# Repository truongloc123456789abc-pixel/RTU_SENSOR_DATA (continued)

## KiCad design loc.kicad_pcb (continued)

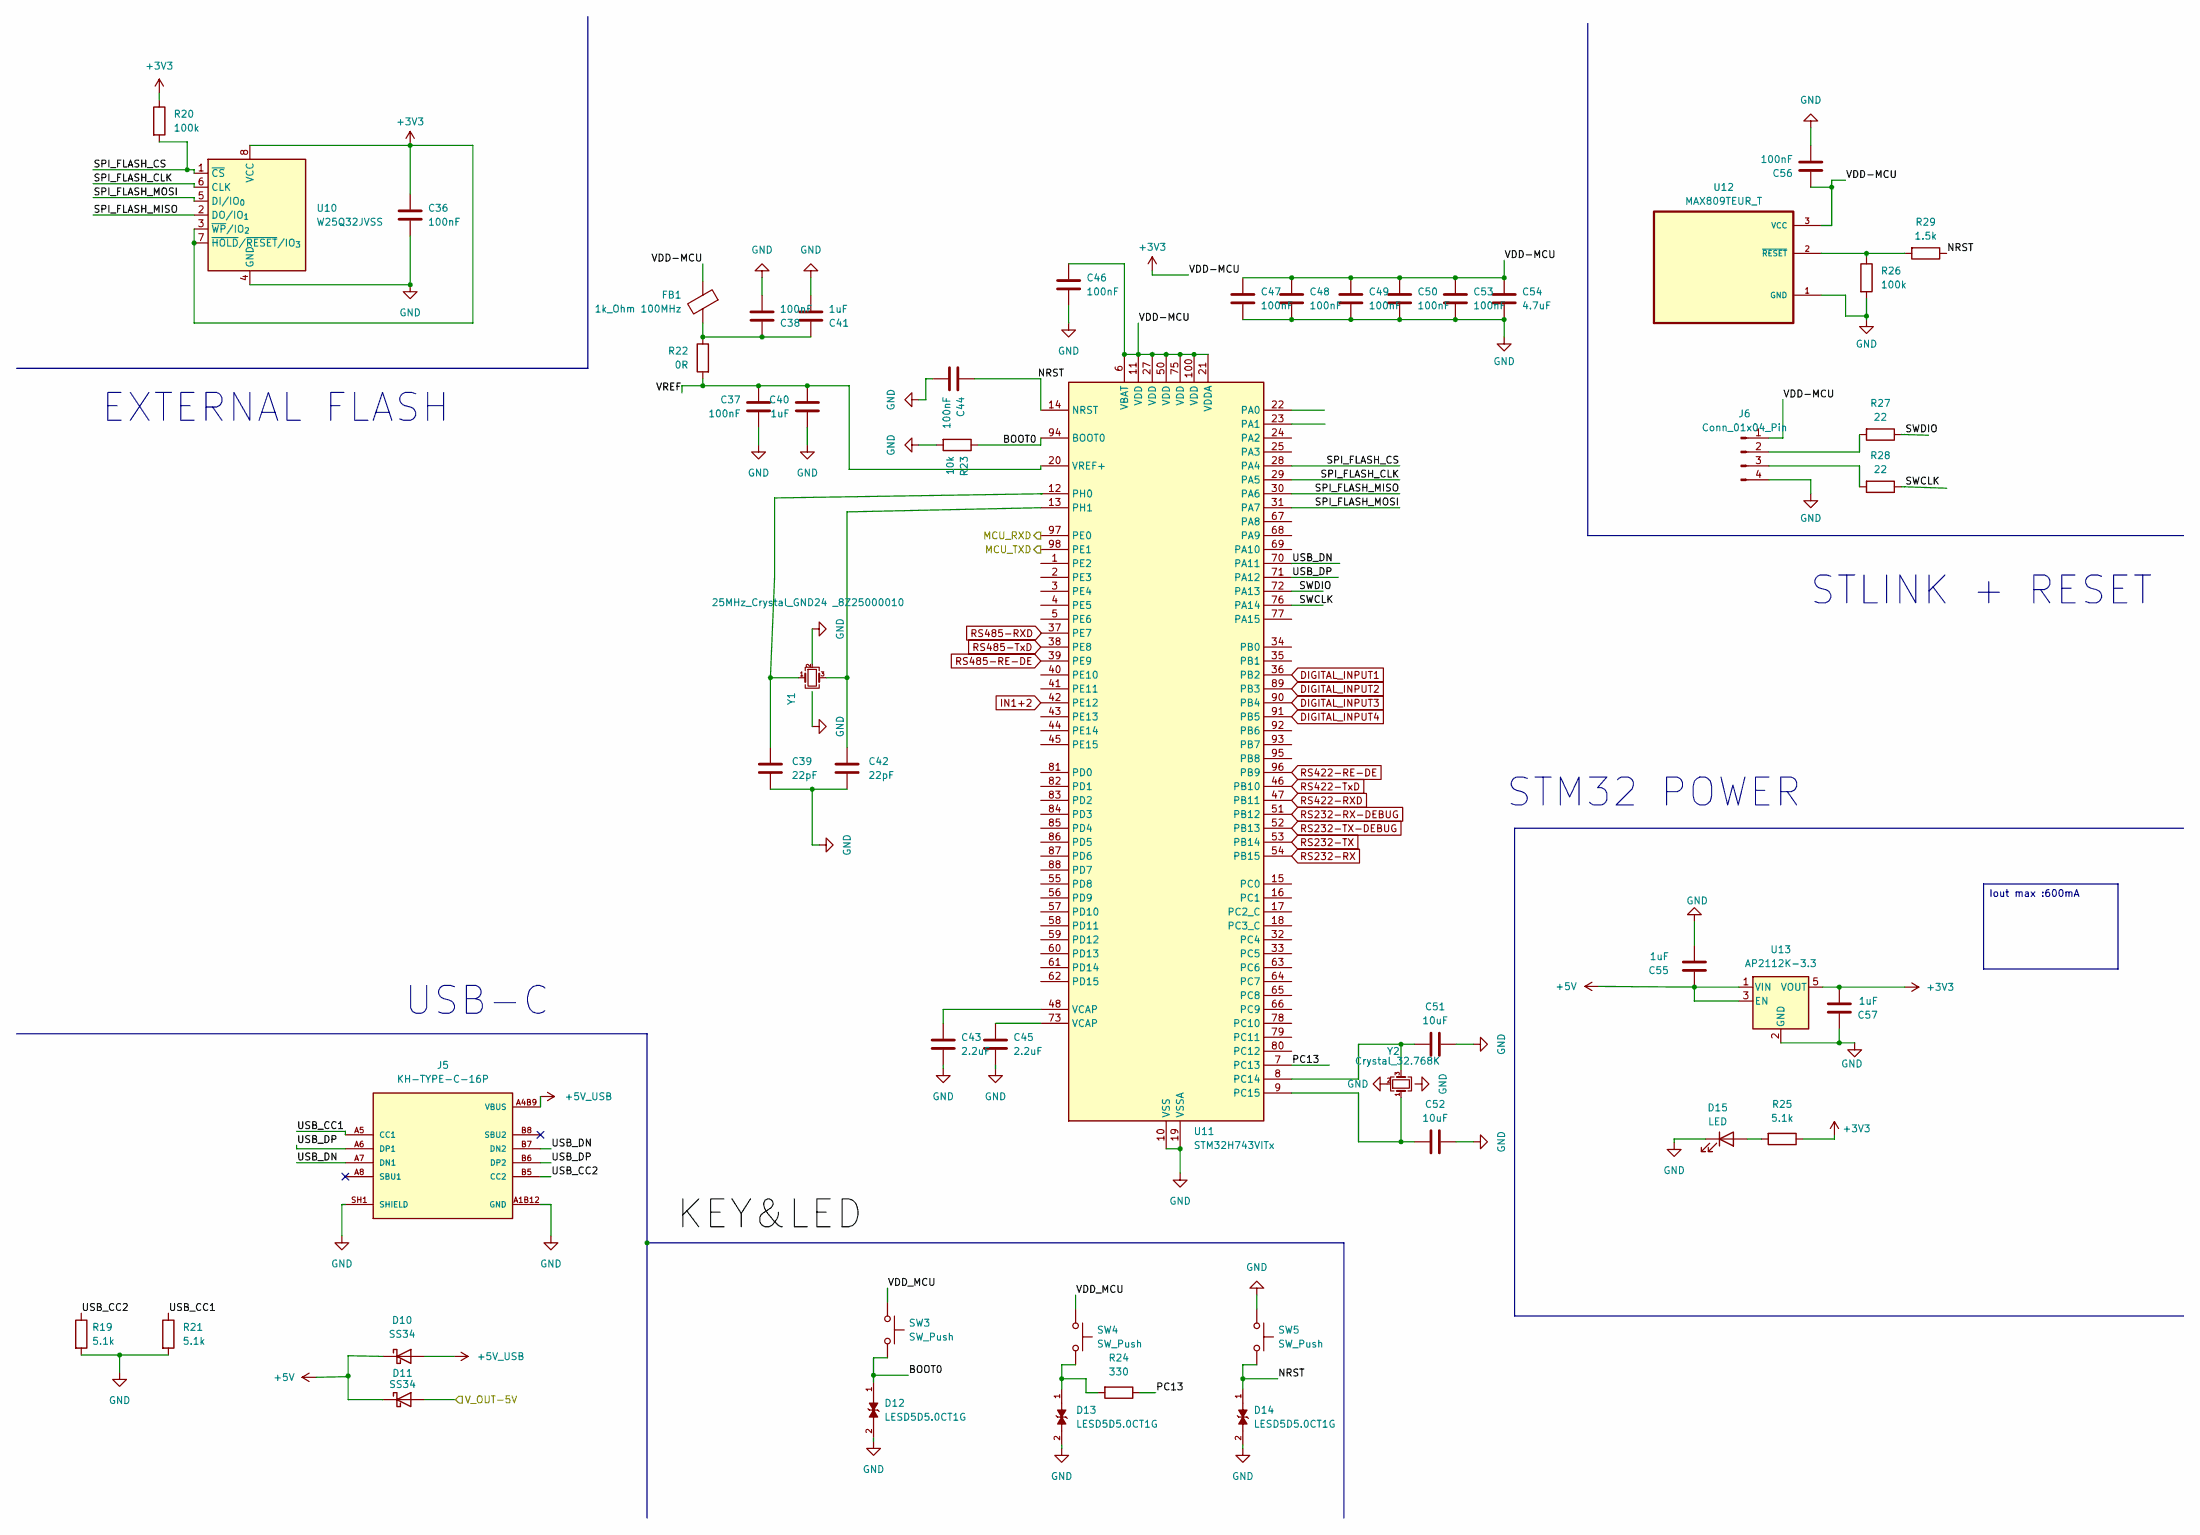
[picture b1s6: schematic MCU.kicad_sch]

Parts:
C36, C37, C38, C44, C46, C47, C48, C49, C50, C53, C56: 100nF; C_0805_2012Metric
C39, C42: 22pF; C_0805_2012Metric_Pad1.18x1.45mm_HandSolder
C40, C41: 1uF; C_0805_2012Metric
C43, C45: 2.2uF; C_0805_2012Metric
C51, C52: 10uF; C_0805_2012Metric
C54: 4.7uF; C_0805_2012Metric
C55: 1uF; C_0805_2012Metric_Pad1.18x1.45mm_HandSolder
C57: 1uF; C_1206_3216Metric_Pad1.33x1.80mm_HandSolder
D10, D11: SS34; D_SMA
D12, D13, D14: LESD5D5.0CT1G; TVS_LESD5D5.0CT1G; PARTREV O
D15: LED; LED_0805_2012Metric
FB1: 1k_Ohm 100MHz; R_0805_2012Metric
J5: KH-TYPE-C-16P; KINGHELM_KH-TYPE-C-16P; PARTREV A0
J6: Conn_01x04_Pin; PinHeader_1x04_P2.54mm_Vertical
R19, R21, R25: 5.1k; R_0805_2012Metric
R20, R26: 100k; R_0805_2012Metric
R22: 0R; R_0805_2012Metric
R23: 10k; R_0805_2012Metric
R24: 330; R_0805_2012Metric
R27, R28: 22; R_0805_2012Metric
R29: 1.5k; R_0805_2012Metric
SW3, SW4, SW5: SW_Push; SW_SPST_B3U-1000P
U10: W25Q32JVSS; SOIC-8_5.3x5.3mm_P1.27mm
U11: STM32H743VITx; LQFP-100_14x14mm_P0.5mm
U12: MAX809TEUR_T; SOT95P237X112-3N
U13: AP2112K-3.3; SOT-23-5
Y1: 25MHz_Crystal_GND24 _8Z25000010; Crystal_SMD_3225-4Pin_3.2x2.5mm
Y2: Crystal_32.768K; Crystal_SMD_3225-4Pin_3.2x2.5mm

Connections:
+3V3: C36.1, C46.1, C47.1, C48.1, C49.1, C50.1, C53.1, C54.1, C56.1, C57.2, FB1.1, J6.1, R20.1, R25.1, U10.3 (~WP/IO_{2}), U10.7 (~HOLD/~RESET/IO_{3}), U10.8 (VCC), U11.6 (VBAT), U11.11 (VDD), U11.21 (VDDA), U11.27 (VDD), U11.50 (VDD), U11.75 (VDD), U11.100 (VDD), U12.3 (VCC), U13.5 (VOUT); also elsewhere on the board
+5V: C55.1, D10.1 (K), D11.1 (K), U13.1 (VIN), U13.3 (EN)
+5V_USB: D10.2 (A), J5.A4B9 (VBUS), J5.A9B4 (VBUS)
/so_do_khoi/RTU_SENSOR_DATA/EC200_INTERFACE/MCU_RXD: U11.97 (PE0); also elsewhere on the board
/so_do_khoi/RTU_SENSOR_DATA/EC200_INTERFACE/MCU_TXD: U11.98 (PE1); also elsewhere on the board
/so_do_khoi/RTU_SENSOR_DATA/MCU/BOOT0: D12.1, R23.1, SW3.2, U11.94 (BOOT0)
/so_do_khoi/RTU_SENSOR_DATA/MCU/NRST: C44.1, D14.1, R29.1, SW5.2, U11.14 (NRST)
/so_do_khoi/RTU_SENSOR_DATA/MCU/PC13: R24.1, U11.7 (PC13)
/so_do_khoi/RTU_SENSOR_DATA/MCU/SPI_FLASH_CLK: U10.6 (CLK), U11.29 (PA5)
/so_do_khoi/RTU_SENSOR_DATA/MCU/SPI_FLASH_CS: R20.2, U10.1 (~CS), U11.28 (PA4)
/so_do_khoi/RTU_SENSOR_DATA/MCU/SPI_FLASH_MISO: U10.2 (DO/IO_{1}), U11.30 (PA6)
/so_do_khoi/RTU_SENSOR_DATA/MCU/SPI_FLASH_MOSI: U10.5 (DI/IO_{0}), U11.31 (PA7)
/so_do_khoi/RTU_SENSOR_DATA/MCU/SWCLK: R28.1, U11.76 (PA14)
/so_do_khoi/RTU_SENSOR_DATA/MCU/SWDIO: R27.1, U11.72 (PA13)
/so_do_khoi/RTU_SENSOR_DATA/MCU/USB_CC1: J5.A5 (CC1), R21.1
/so_do_khoi/RTU_SENSOR_DATA/MCU/USB_CC2: J5.B5 (CC2), R19.1
/so_do_khoi/RTU_SENSOR_DATA/MCU/USB_DN: J5.A7 (DN1), J5.B7 (DN2), U11.70 (PA11)
/so_do_khoi/RTU_SENSOR_DATA/MCU/USB_DP: J5.A6 (DP1), J5.B6 (DP2), U11.71 (PA12)
/so_do_khoi/RTU_SENSOR_DATA/MCU/VDD_MCU: SW3.1, SW4.1
/so_do_khoi/RTU_SENSOR_DATA/MCU/VREF: C37.1, C40.1, R22.2, U11.20 (VREF+)
/so_do_khoi/RTU_SENSOR_DATA/MCU/V_OUT-5V: D11.2 (A); also elsewhere on the board
DIGITAL_INPUT1: U11.36 (PB2); also elsewhere on the board
DIGITAL_INPUT2: U11.89 (PB3); also elsewhere on the board
DIGITAL_INPUT3: U11.90 (PB4); also elsewhere on the board
DIGITAL_INPUT4: U11.91 (PB5); also elsewhere on the board
GND: C36.2, C37.2, C38.2, C39.2, C40.2, C41.2, C42.2, C43.2, C44.2, C45.2, C46.2, C47.2, C48.2, C49.2, C50.2, C51.2, C52.2, C53.2, C54.2, C55.2, C56.2, C57.1, D12.2, D13.2, D14.2, D15.1 (K), J5.A1B12 (GND), J5.A12B1 (GND), J5.SH1 (SHIELD), J5.SH2 (SHIELD), J5.SH3 (SHIELD), J5.SH4 (SHIELD), J6.4, R19.2, R21.2, R23.2, R26.2, SW5.1, U10.4 (GND), U11.10 (VSS), U11.19 (VSSA), U11.26 (VSS), U11.49 (VSS), U11.74 (VSS), U11.99 (VSS), U12.1 (GND), U13.2 (GND), Y1.2 (G), Y1.4 (G), Y2.2 (G), Y2.4 (G); also elsewhere on the board
IN1+2: U11.42 (PE12); also elsewhere on the board
unnamed: C38.1, C41.1, FB1.2, R22.1
unnamed: C43.1, U11.48 (VCAP)
unnamed: C45.1, U11.73 (VCAP)
unnamed: D13.1, R24.2, SW4.2
unnamed: D15.2 (A), R25.2
unnamed: J6.2, R27.2
unnamed: J6.3, R28.2
unnamed: C51.1, U11.8 (PC14), Y2.3
unnamed: C52.1, U11.9 (PC15), Y2.1
unnamed: C39.1, U11.12 (PH0), Y1.1
unnamed: C42.1, U11.13 (PH1), Y1.3
unnamed: R26.1, R29.2, U12.2 (~RESET)
RS232-RX: U11.54 (PB15); also elsewhere on the board
RS232-RX-DEBUG: U11.51 (PB12); also elsewhere on the board
RS232-TX: U11.53 (PB14); also elsewhere on the board
RS232-TX-DEBUG: U11.52 (PB13); also elsewhere on the board
RS422-RE-DE: U11.96 (PB9); also elsewhere on the board
RS422-RXD: U11.47 (PB11); also elsewhere on the board
RS422-TxD: U11.46 (PB10); also elsewhere on the board
RS485-RE-DE: U11.39 (PE9); also elsewhere on the board
RS485-RXD: U11.37 (PE7); also elsewhere on the board
RS485-TxD: U11.38 (PE8); also elsewhere on the board

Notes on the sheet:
STLINK + RESET
USB-C
STM32 POWER
EXTERNAL FLASH
Iout max :600mA

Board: 2 copper layers, 189 parts (0 on the bottom side), 149 nets, no tracks yet.
